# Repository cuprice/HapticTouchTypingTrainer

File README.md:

## タイピング練習用キーボード基板 Haptic Touch Typing Trainer (Prototype)

# これは何？
What is this?

A haptic and audio-guided touch typing trainer that tells you which key to press next through vibration and sound — no need to look at your hands.

振動と音で次に押すべきキーを知らせる、触覚と聴覚を使ったタッチタイピング練習機です。

[ビルドガイド](BUILDGUIDE.md)を作りましたのでご覧ください。

[おまけ](#おまけ)の項目にはSMDをできるだけ使用したバージョンのデータがあります。

I made a [build guide](BUILDGUIDE.md).

There is a version that uses as many SMD parts as possible in the [Extras section](#おまけ).

# はじめに

このリポジトリは回路・プログラミング初学者の学習用です。あたたかく見守っていただけると嬉しいです。

これは、プログラミングや回路の初心者である私が、自分なりに学びながら作ってみた実装基板です。  
8つのキーに振動する部品を付け、目で確認しなくてもどこを押せば良いかがわかる機能を目指しました。
~~公開しようと思ったきっかけは、似たようなアイデアのタイピング練習機を見つけることができなかったためです。~~

触覚を利用した複雑なタッチタイピングの練習機械が他にもあることを知り、私はまだまだ勉強不足であると思いました。もしお嫌でなければ、学習の活動を見守っていただければ幸いです。

このリポジトリでは、タイピング練習を目的としたキーボード基板の設計データを公開しています。  
基板はKiCad 9.0で設計されています。振動するキー順番を変更するには、Arduinoのスケッチを編集する必要があります。

ただし、現在はアイデア段階であり、完全な完成品ではありません。今後の改善や追加機能に関しては更新を行う予定です。

This repository is for beginners who are learning circuits and programming.
I’d be happy if you could kindly support it.

This is a keyboard I made while learning programming and circuits by myself.
I am still a beginner, but I tried my best to build it.

I added small parts that can vibrate to 8 keys.
This way, you can feel which key to press without looking.

~~I decided to share this because I couldn't find a similar typing practice device online.~~

I learned that there are other machines that use touch to practice touch typing in a complex way, and I felt that I still have a lot to learn.
If you don’t mind, I would be happy if you could watch over my learning.

In this repository, I show the design data for this keyboard.
I made the design using KiCad 9.0.
If you want to change the order of the vibrating keys, you need to change the Arduino program.

Please note that this is still just an idea, not a finished product.
I want to improve it and add more features in the future.

---

## 特徴

- 10列、3段のキー(計30個)による練習用構成
- リセットスイッチ付き
- Cherry MX対応
- Arduino Nano Everyで完璧ではありませんが、一応動作確認済みです (後継機のモデルは動作未確認)
- KiCad 9.0で基板設計
- 基板サイズ：約261.1mm × 81.5mm(捨て基板除く)
- 電源：Arduino Nano Every経由でのUSB給電

This is a practice keyboard layout with 30 keys, arranged in 10 columns and 3 rows.
It includes a reset switch. It's compatible with Cherry MX switches. I've confirmed it works with the Arduino nano every, although it's not perfect. I haven't tested it with newer Arduino models. The circuit board was designed using KiCad 9.0. The board size is about 261.1mm × 81.5mm, and it's powered by USB through the Arduino nano every.

どの段のキーを押せば良いかを、3段階のブザー音で教えるためのコードを加筆修正しました。上の段ならば3回鳴り、下の段ならば１回鳴り、真ん中の段なら２回鳴るという仕組みにしました。振動モーターがないキーの場合は、振動する長さを変えて位置を知らせるようにしました。

I changed the code to use three kinds of buzzer sounds to tell the user which row of keys to press.
If the key is on the top row, the buzzer beeps three times.
If the key is on the bottom row, it beeps one time.
If the key is on the middle row, it beeps two times.
For keys that do not have a vibration motor, the device changes the length of the vibration to show the position.

---

## ファイル構成

~~~

TypingTrainer/
    ├── TYPING-TRAINER-V5-SMD/ # KiCad設計ファイル
    ├── TYPING-TRAINER-V5-SMD.zip # ガーバーデータ（基板製造用）
    ├── TrainerV5-smd/ # Arduinoスケッチ 通常版
    ├── TrainerV5-smd2/ # Arduinoスケッチ 切替式例文プリセットタイプ
    ├── numorder.py # キーの順番を決めるPythonスクリプト
    ├── keycap.stl # 3Dプリンタ用、穴有りキャップ
    ├── images/ # 写真・完成図
    ├── docs/ # 部品表・座標データなど
    ├── OldVersion-Uno # 旧バージョン、Uno用
    ├── OldVersion-Nano # 旧バージョン、Nano用
    ├── README.md # このファイル
    ├── BUILDGUIDE.md # ビルドガイド
    └── Haptic Touch Typing Trainer SMD-package/ # SMD版データ

~~~

---

## 完成イメージ、回路図、動作の様子

[動作の様子](images/working.mp4)

[モーターの動き](images/shaker.mp4)

---

## 使い方
1. ガーバーファイルをJLCPCBなどで製造依頼
2. 回路図などを見ながら部品を実装
3. Arduino Nano EveryをUSBケーブルでPCと接続
4. PCからArduinoへ、ファームウェアを書き込み

組み立ての際は、[ビルドガイド](BUILDGUIDE.md)を参照してください。

---

## 必要部品

| Value               | Reference      | Qty | 備考                                           | 画像 |
|---------------------|----------------|-----|------------------------------------------------|------|
| Arduino Nano Every  | A1             | 1   | マイクロコントローラー（ソケットピン経由で実装） |  |
| Passive Buzzer      | BZ1            | 1   | パッシブブザー                                         |  |
| 1N4148              | D1 〜 D30      | 30  | スイッチのマトリックス用ダイオード             |  |
| LED                 | D100, D101     | 2   | インジケーターLED                              |  |
| Motor DC            | M1 〜 M8       | 8   | DCモーター                                     |  |
| Resist 10k                 | R1 〜 R12      | 12  | 抵抗（10kΩ）                                   |  |
| Resist 330                 | R13, R14       | 2   | 抵抗（330Ω, LED電流制限用）                    |  |
| Cherry MX Switch    | SW1 〜 SW30    | 30  | Cherry MX互換キースイッチ(キーキャップはお好みで)                      |  |
| 2pin Button         | SW100, SW101   | 2   | 2ピンのタクトスイッチなど                      |  |
| MCP23017_SP         | U2             | 1   | I/Oエキスパンダー（ICソケットの上に実装）      |  |
| TerminalBlock         | M1 〜 M8             | 8   | ターミナルブロック(裏面実装)      |  |
| SW socket         | SW1 〜 SW30             | 30   | キースイッチソケット(裏面実装)      |  |

---

## KiCad情報

- KiCad バージョン: 9.0
- 古いバージョンでは一部ファイルが開けない可能性があります。
- 最新バージョンでの動作は未確認です。

使用したライブラリURL
- ブザーフットプリント
 https://jp.sameskydevices.com/product/resource/pcbfootprint/cmt-9648-85t
- キースイッチフットプリント
 https://github.com/daprice/keyswitches.pretty?tab=readme-ov-file

---

## ライセンス

この基板デザインは MIT ライセンスで公開しています。  

---

## よくある質問

準備中
**Q. ？**  
A. 

---

## 注意事項

- 初心者が学びながら作ったものなので、不完全な点もあるかもしれません。
- Arduinoスケッチのコード作成に、生成AI（ChatGPT）を補助的に活用しました。

---

## Special Thanks

- ネット上のチュートリアルや電子工作記事の皆さま

---

## おまけ

タッチタイピング練習基板の別バージョンを作ってみました。
なるべく自分ではんだ付けをしないようにするためにSMD品を取り入れて、RP2040zeroを実装しました。
そしてスイッチプレートを試しに3Dプリンターで作りました。

I made another version of my touch typing practice board.
I used some SMD parts and added an RP2040-Zero so that I would not have to do too much soldering myself.
I also tried making a switch plate with a 3D printer.

[SMD版ビルドガイド](HapticTouchTypingTrainerSMD-package/HapticTouchTypingTrainerSMD.md)

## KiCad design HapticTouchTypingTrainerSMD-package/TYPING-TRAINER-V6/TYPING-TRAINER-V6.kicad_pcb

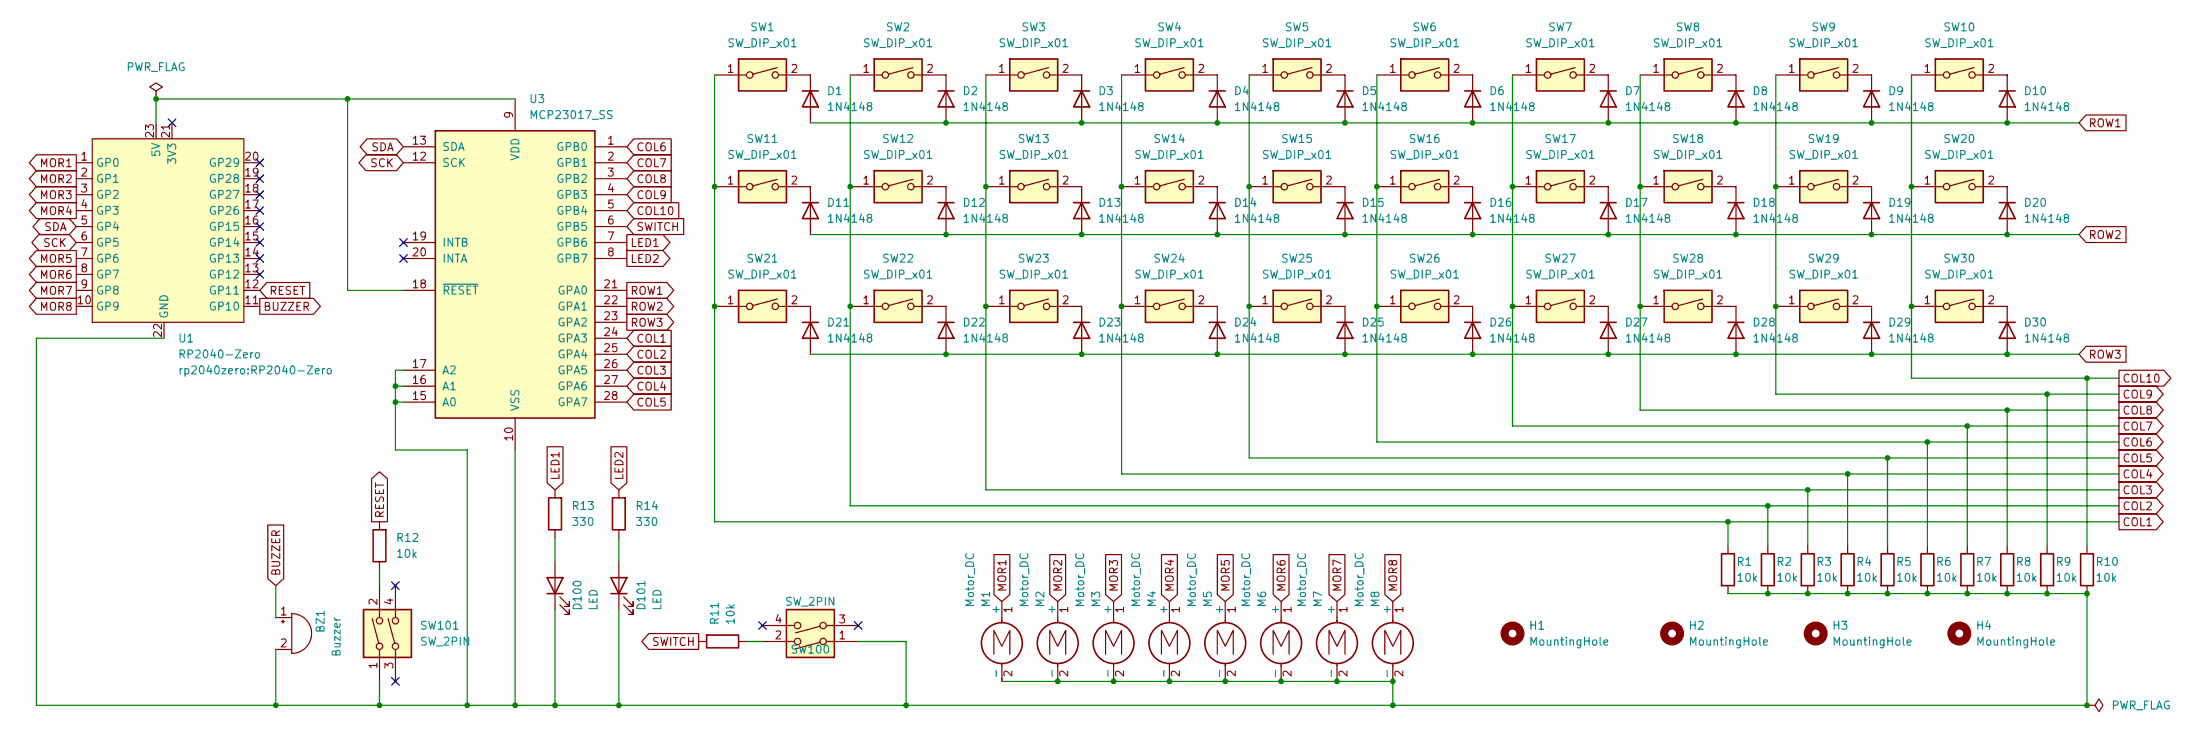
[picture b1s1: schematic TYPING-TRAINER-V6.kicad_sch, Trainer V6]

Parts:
BZ1: Buzzer; XDCR_CMT-9648-85T; LCSC C22359749
D1, D2, D3, D4, D5, D6, D7, D8, D9, D10, D11, D12, D13, D14, D15, D16, D17, D18, D19, D20, D21, D22, D23, D24, D25, D26, D27, D28, D29, D30: 1N4148; D_SOD-123; LCSC C2099
D100, D101: LED; LED_0603_1608Metric; LCSC C88163
H1, H2, H3, H4: MountingHole; MountingHole_3.2mm_M3
M1, M2, M3, M4, M5, M6, M7, M8: Motor_DC; TerminalBlock_MaiXu_MX126-5.0-02P_1x02_P5.00mm
R1, R2, R3, R4, R5, R6, R7, R8, R9, R10, R11, R12: 10k; R_0603_1608Metric; LCSC C130232
R13, R14: 330; R_0603_1608Metric; LCSC C175652
SW1, SW2, SW3, SW4, SW5, SW6, SW7, SW8, SW9, SW10, SW11, SW12, SW13, SW14, SW15, SW16, SW17, SW18, SW19, SW20, SW21, SW22, SW23, SW24, SW25, SW26, SW27, SW28, SW29, SW30: SW_DIP_x01; Kailh_socket_MX; LCSC C41430893
SW100, SW101: SW_2PIN; SW_SPST_SKQG_WithStem
U1: RP2040-Zero
U3: MCP23017_SS; SSOP-28_5.3x10.2mm_P0.65mm

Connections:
BUZZER: BZ1.1 (+), U1.11 (GP10)
COL1: R1.1, SW1.1, SW11.1, SW21.1, U3.24 (GPA3)
COL2: R2.1, SW2.1, SW12.1, SW22.1, U3.25 (GPA4)
COL3: R3.1, SW3.1, SW13.1, SW23.1, U3.26 (GPA5)
COL4: R4.1, SW4.1, SW14.1, SW24.1, U3.27 (GPA6)
COL5: R5.1, SW5.1, SW15.1, SW25.1, U3.28 (GPA7)
COL6: R6.1, SW6.1, SW16.1, SW26.1, U3.1 (GPB0)
COL7: R7.1, SW7.1, SW17.1, SW27.1, U3.2 (GPB1)
COL8: R8.1, SW8.1, SW18.1, SW28.1, U3.3 (GPB2)
COL9: R9.1, SW9.1, SW19.1, SW29.1, U3.4 (GPB3)
COL10: R10.2, SW10.1, SW20.1, SW30.1, U3.5 (GPB4)
LED1: R13.2, U3.7 (GPB6)
LED2: R14.2, U3.8 (GPB7)
MOR1: M1.1 (+), U1.1 (GP0)
MOR2: M2.1 (+), U1.2 (GP1)
MOR3: M3.1 (+), U1.3 (GP2)
MOR4: M4.1 (+), U1.4 (GP3)
MOR5: M5.1 (+), U1.7 (GP6)
MOR6: M6.1 (+), U1.8 (GP7)
MOR7: M7.1 (+), U1.9 (GP8)
MOR8: M8.1 (+), U1.10 (GP9)
unnamed: BZ1.2 (-), D100.1 (K), D101.1 (K), M1.2 (-), M2.2 (-), M3.2 (-), M4.2 (-), M5.2 (-), M6.2 (-), M7.2 (-), M8.2 (-), R1.2, R2.2, R3.2, R4.2, R5.2, R6.2, R7.2, R8.2, R9.2, R10.1, SW100.1, SW101.1, U1.22 (GND), U3.10 (VSS), U3.15 (A0), U3.16 (A1), U3.17 (A2)
unnamed: D1.1 (K), SW1.2
unnamed: D2.1 (K), SW2.2
unnamed: D3.1 (K), SW3.2
unnamed: D4.1 (K), SW4.2
unnamed: D5.1 (K), SW5.2
unnamed: D6.1 (K), SW6.2
unnamed: D7.1 (K), SW7.2
unnamed: D8.1 (K), SW8.2
unnamed: D9.1 (K), SW9.2
unnamed: D10.1 (K), SW10.2
unnamed: D11.1 (K), SW11.2
unnamed: D12.1 (K), SW12.2
unnamed: D13.1 (K), SW13.2
unnamed: D14.1 (K), SW14.2
unnamed: D15.1 (K), SW15.2
unnamed: D16.1 (K), SW16.2
unnamed: D17.1 (K), SW17.2
unnamed: D18.1 (K), SW18.2
unnamed: D19.1 (K), SW19.2
unnamed: D20.1 (K), SW20.2
unnamed: D21.1 (K), SW21.2
unnamed: D22.1 (K), SW22.2
unnamed: D23.1 (K), SW23.2
unnamed: D24.1 (K), SW24.2
unnamed: D25.1 (K), SW25.2
unnamed: D26.1 (K), SW26.2
unnamed: D27.1 (K), SW27.2
unnamed: D28.1 (K), SW28.2
unnamed: D29.1 (K), SW29.2
unnamed: D30.1 (K), SW30.2
unnamed: D100.2 (A), R13.1
unnamed: D101.2 (A), R14.1
unnamed: R11.1, SW100.2
unnamed: R12.1, SW101.2
unnamed: U1.23 (5V), U3.9 (VDD), U3.18 (~RESET)
RESET: R12.2, U1.12 (GP11)
ROW1: D1.2 (A), D2.2 (A), D3.2 (A), D4.2 (A), D5.2 (A), D6.2 (A), D7.2 (A), D8.2 (A), D9.2 (A), D10.2 (A), U3.21 (GPA0)
ROW2: D11.2 (A), D12.2 (A), D13.2 (A), D14.2 (A), D15.2 (A), D16.2 (A), D17.2 (A), D18.2 (A), D19.2 (A), D20.2 (A), U3.22 (GPA1)
ROW3: D21.2 (A), D22.2 (A), D23.2 (A), D24.2 (A), D25.2 (A), D26.2 (A), D27.2 (A), D28.2 (A), D29.2 (A), D30.2 (A), U3.23 (GPA2)
SCK: U1.6 (GP5), U3.12 (SCK)
SDA: U1.5 (GP4), U3.13 (SDA)
SWITCH: R11.2, U3.6 (GPB5)

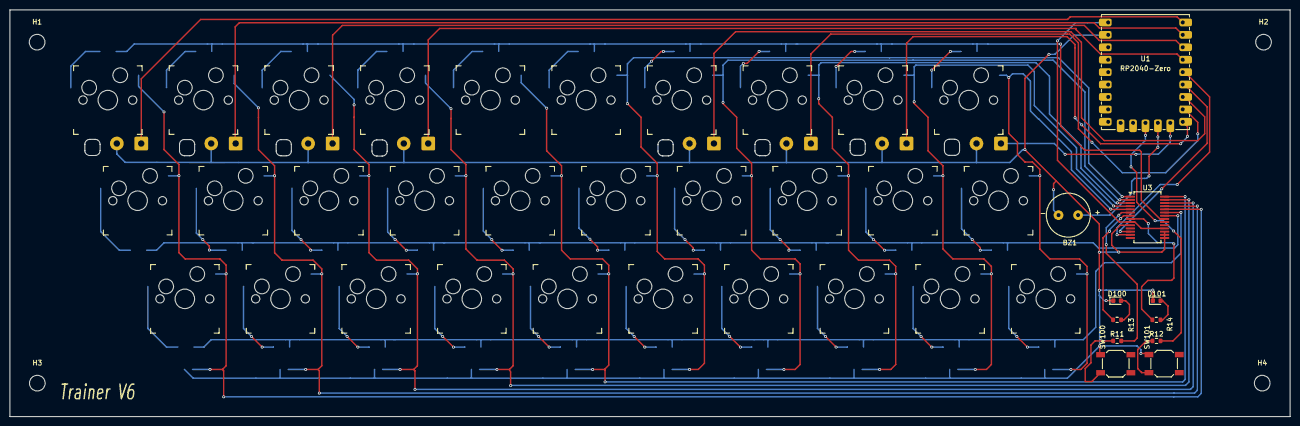
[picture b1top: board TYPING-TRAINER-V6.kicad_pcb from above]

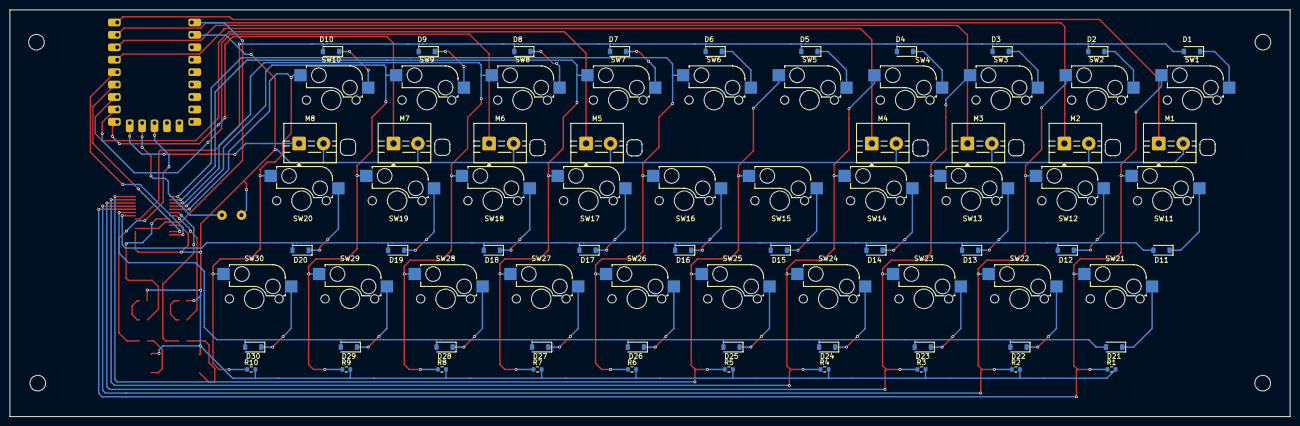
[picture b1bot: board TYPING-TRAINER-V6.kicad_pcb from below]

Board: 2 copper layers, 261.8 x 83.2 mm, 93 parts (48 on the bottom side), 64 nets.

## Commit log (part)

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2026-01-24 2026 1st update
2026-03-29 SMD version
2026-03-30 Readme.md update
2026-04-13 Text Generator
